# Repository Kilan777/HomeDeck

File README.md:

# Jarvis HomeDeck

> **Public mirror.** This is a snapshot of the private working repo (commit `f1d429f`). Some private parts of the software are not included.

A self-built voice assistant with a screen: a Raspberry Pi Compute Module 4 carrier PCB that bolts to the 7-inch
Raspberry Pi Touch Display 2, plus the software that turns it into "Jarvis". Personal project by Kilan.

The board carries the CM4, USB-C PD power, three 5 V bucks, a stereo class-D amplifier, two MEMS microphones,
a Camera Module 3 connector, CO2 / temperature / humidity / pressure / VOC sensors, an RGB LED bar and an external
WS2812B strip header, a fan header, buttons, a Qwiic-style I2C header, microSD, USB-A and a second USB-C.

The software is a single Python service with a module per feature and a touch UI in Chromium, plus a phone app
served on a personal domain behind Google sign-in. Voice runs on a local wake word and hosted speech models;
everything that is a command (timers, lights, music, volume, math) is handled on the device without a model.

| Folder | Contents |
|---|---|
| `kicad/` | KiCad project: hierarchical schematic (9 sheets), 4-layer routed PCB, project symbols and footprints, DRC rules |
| `tools/circuit.py` | The single source the schematic, netlist and BOM are generated from. Edit this, not the KiCad files |
| `out/` | Gerbers, JLCPCB BOM and pick-and-place, schematic PDF, board renders, DRC report (rev A as ordered) |
| `docs/` | Hardware docs: `README.md` (board overview), `ARCHITECTURE.md`, `BRINGUP.md`, `ORIENTATION.md`, and `PCB_ISSUES.md` (what went wrong on rev A and what rev B should change) |
| `software/homedeck/` | The assistant: `server.py`, `modules/`, `web/`, `install/`. See `docs/SOFTWARE.md` |
| `software/homedeck_ui.py` | The original bench dashboard used for bring-up (retired) |

## Status

- Rev A board #1 is fully working and in daily use, running at 9 V PD after two solder-jumper changes.
  Rev A board #2 is assembled and untested. Findings and the rev B list are in `docs/PCB_ISSUES.md`.
- Software is feature complete for daily use: home screen, Jarvis voice, Spotify (full client), YouTube (ad-free
  native player), air quality with history, timers, alarms, reminders, lists, calendar, countdowns, bikes, transit,
  flights radar, lights, fan, sleep sounds, guest card with Wi-Fi QR,
  presence, Wi-Fi setup, on-screen keyboard. See `docs/SOFTWARE.md`.

## Quick start

Hardware: order from `out/` (JLCPCB 4-layer, two-sided assembly), read `docs/BRINGUP.md`, then apply the rev A
fixes in `docs/PCB_ISSUES.md` before first power-on (the 9 V jumper setting matters).

Software, on the Pi:

```
rsync -a software/homedeck/ kilan@homedeck.local:~/hd/
ssh kilan@homedeck.local 'cd ~/hd && bash install.sh'
```

Then open Settings on the device for location, Wi-Fi, Spotify, calendar feeds and the API keys the optional
features need (Groq for voice, 511.org for Muni). Secrets live only on the device in `/var/lib/homedeck/config.json`
and are never in this repository.

## Privacy

This repository is private. It contains no credentials, tokens or Wi-Fi passwords. The device redacts secrets
from every API response, the phone app requires Google sign-in, and there is no VPN or third-party relay involved.

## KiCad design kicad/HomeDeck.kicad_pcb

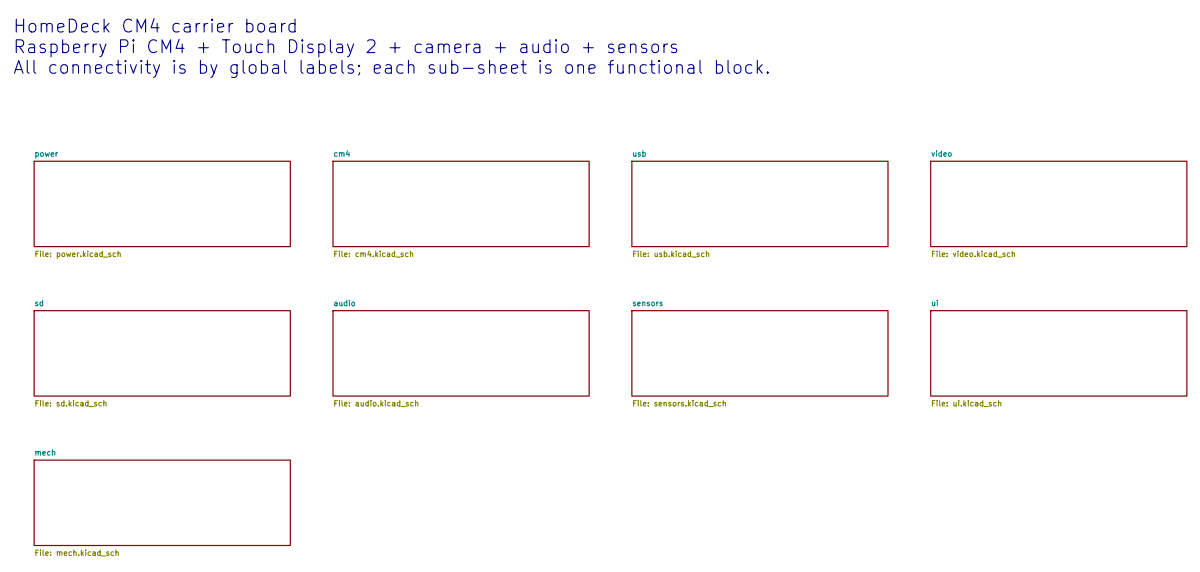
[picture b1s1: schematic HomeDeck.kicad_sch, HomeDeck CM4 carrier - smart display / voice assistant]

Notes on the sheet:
HomeDeck CM4 carrier board Raspberry Pi CM4 + Touch Display 2 + camera + audio + sensors All connectivity is by global labels; each sub-sheet is one functional block.

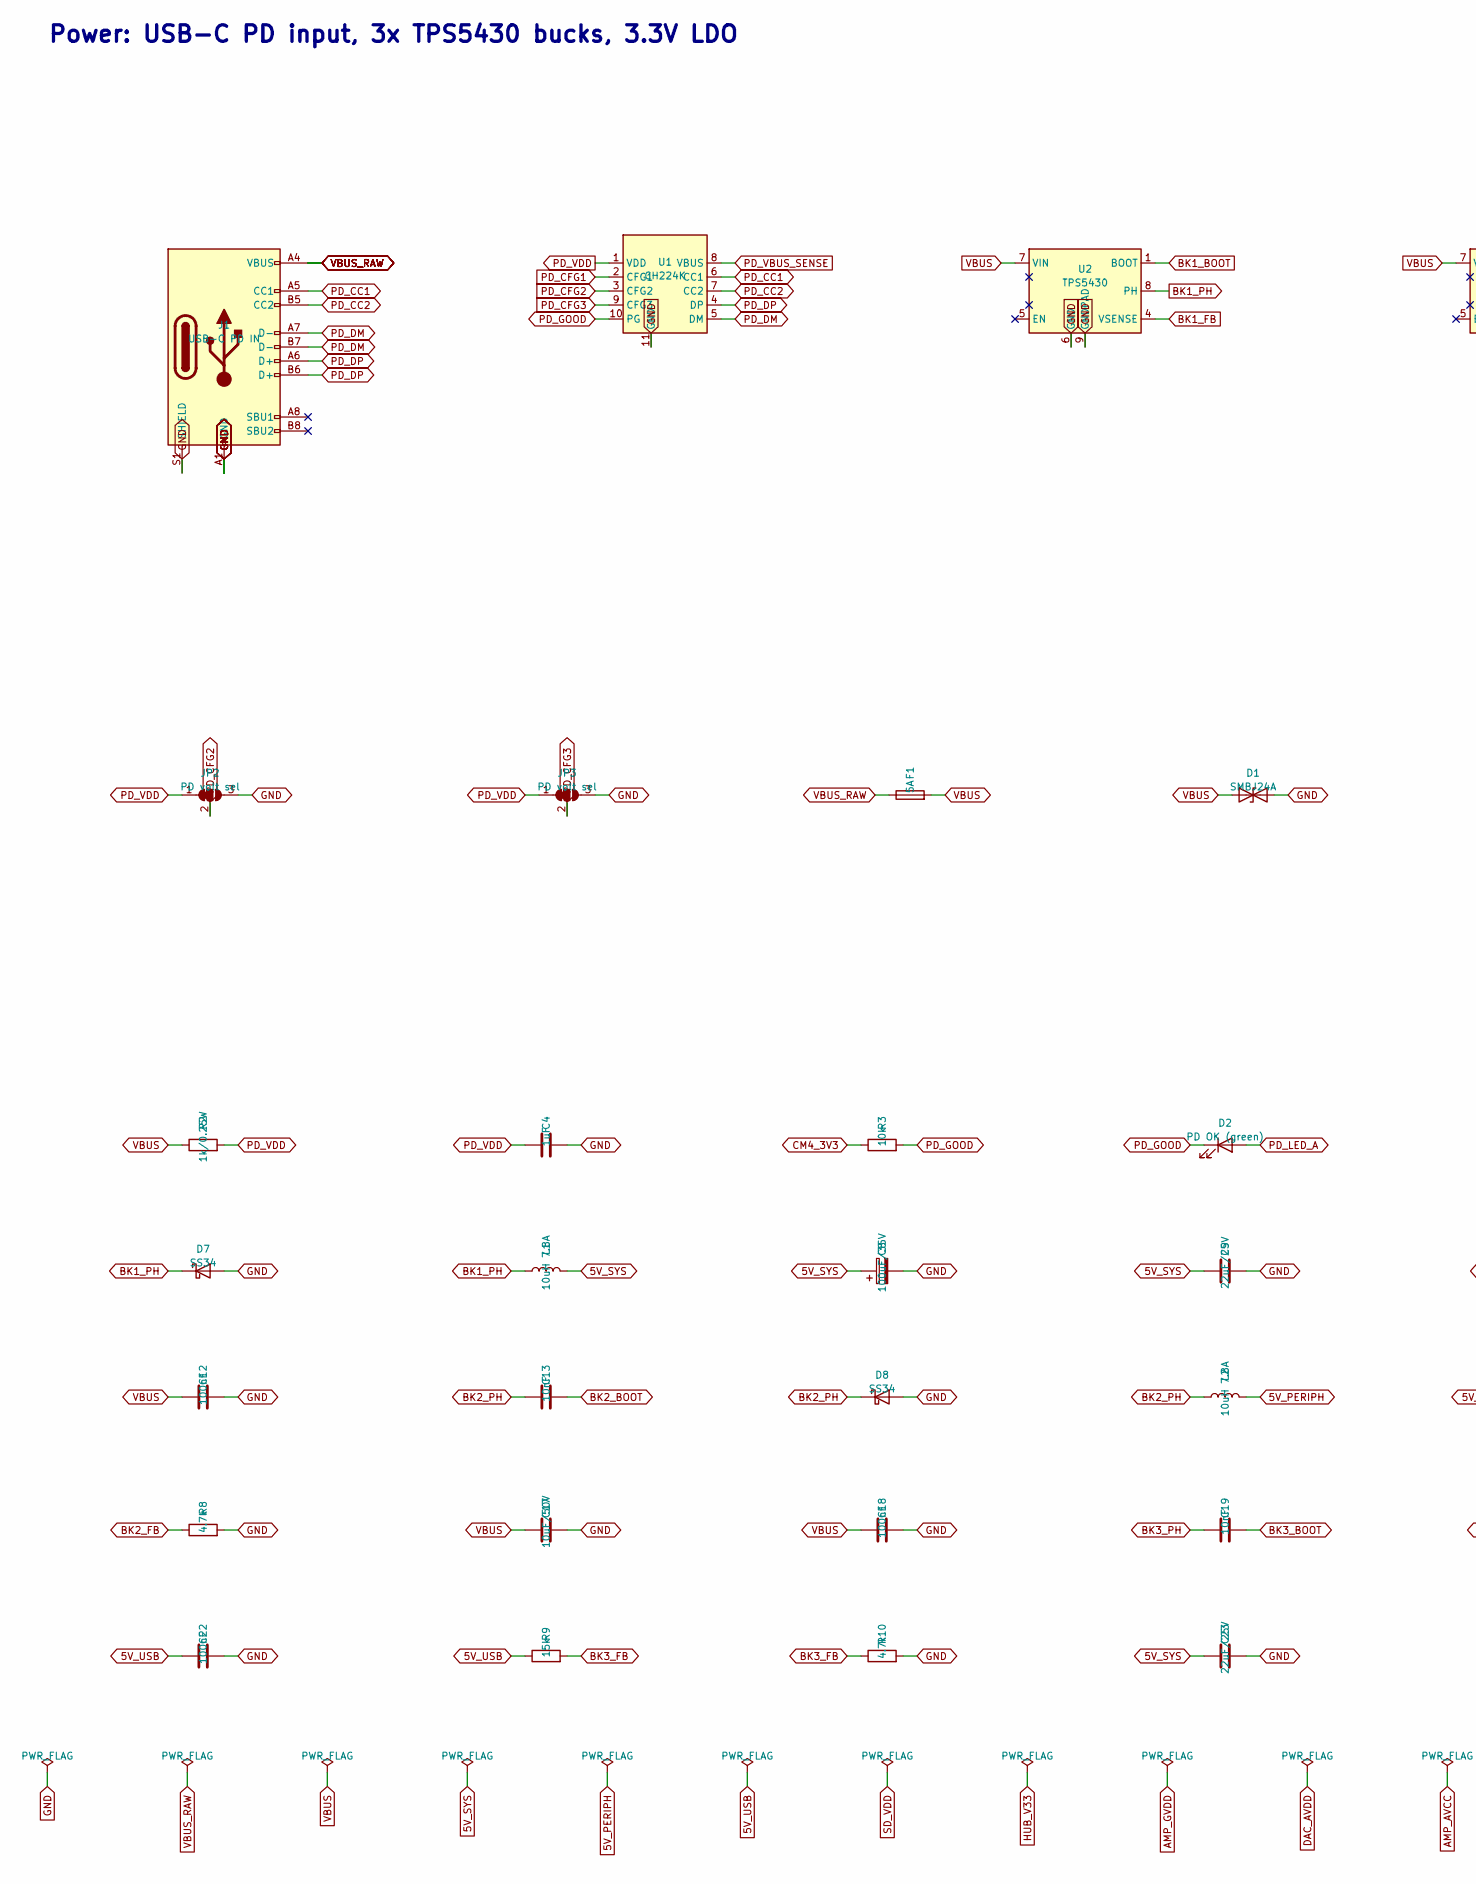
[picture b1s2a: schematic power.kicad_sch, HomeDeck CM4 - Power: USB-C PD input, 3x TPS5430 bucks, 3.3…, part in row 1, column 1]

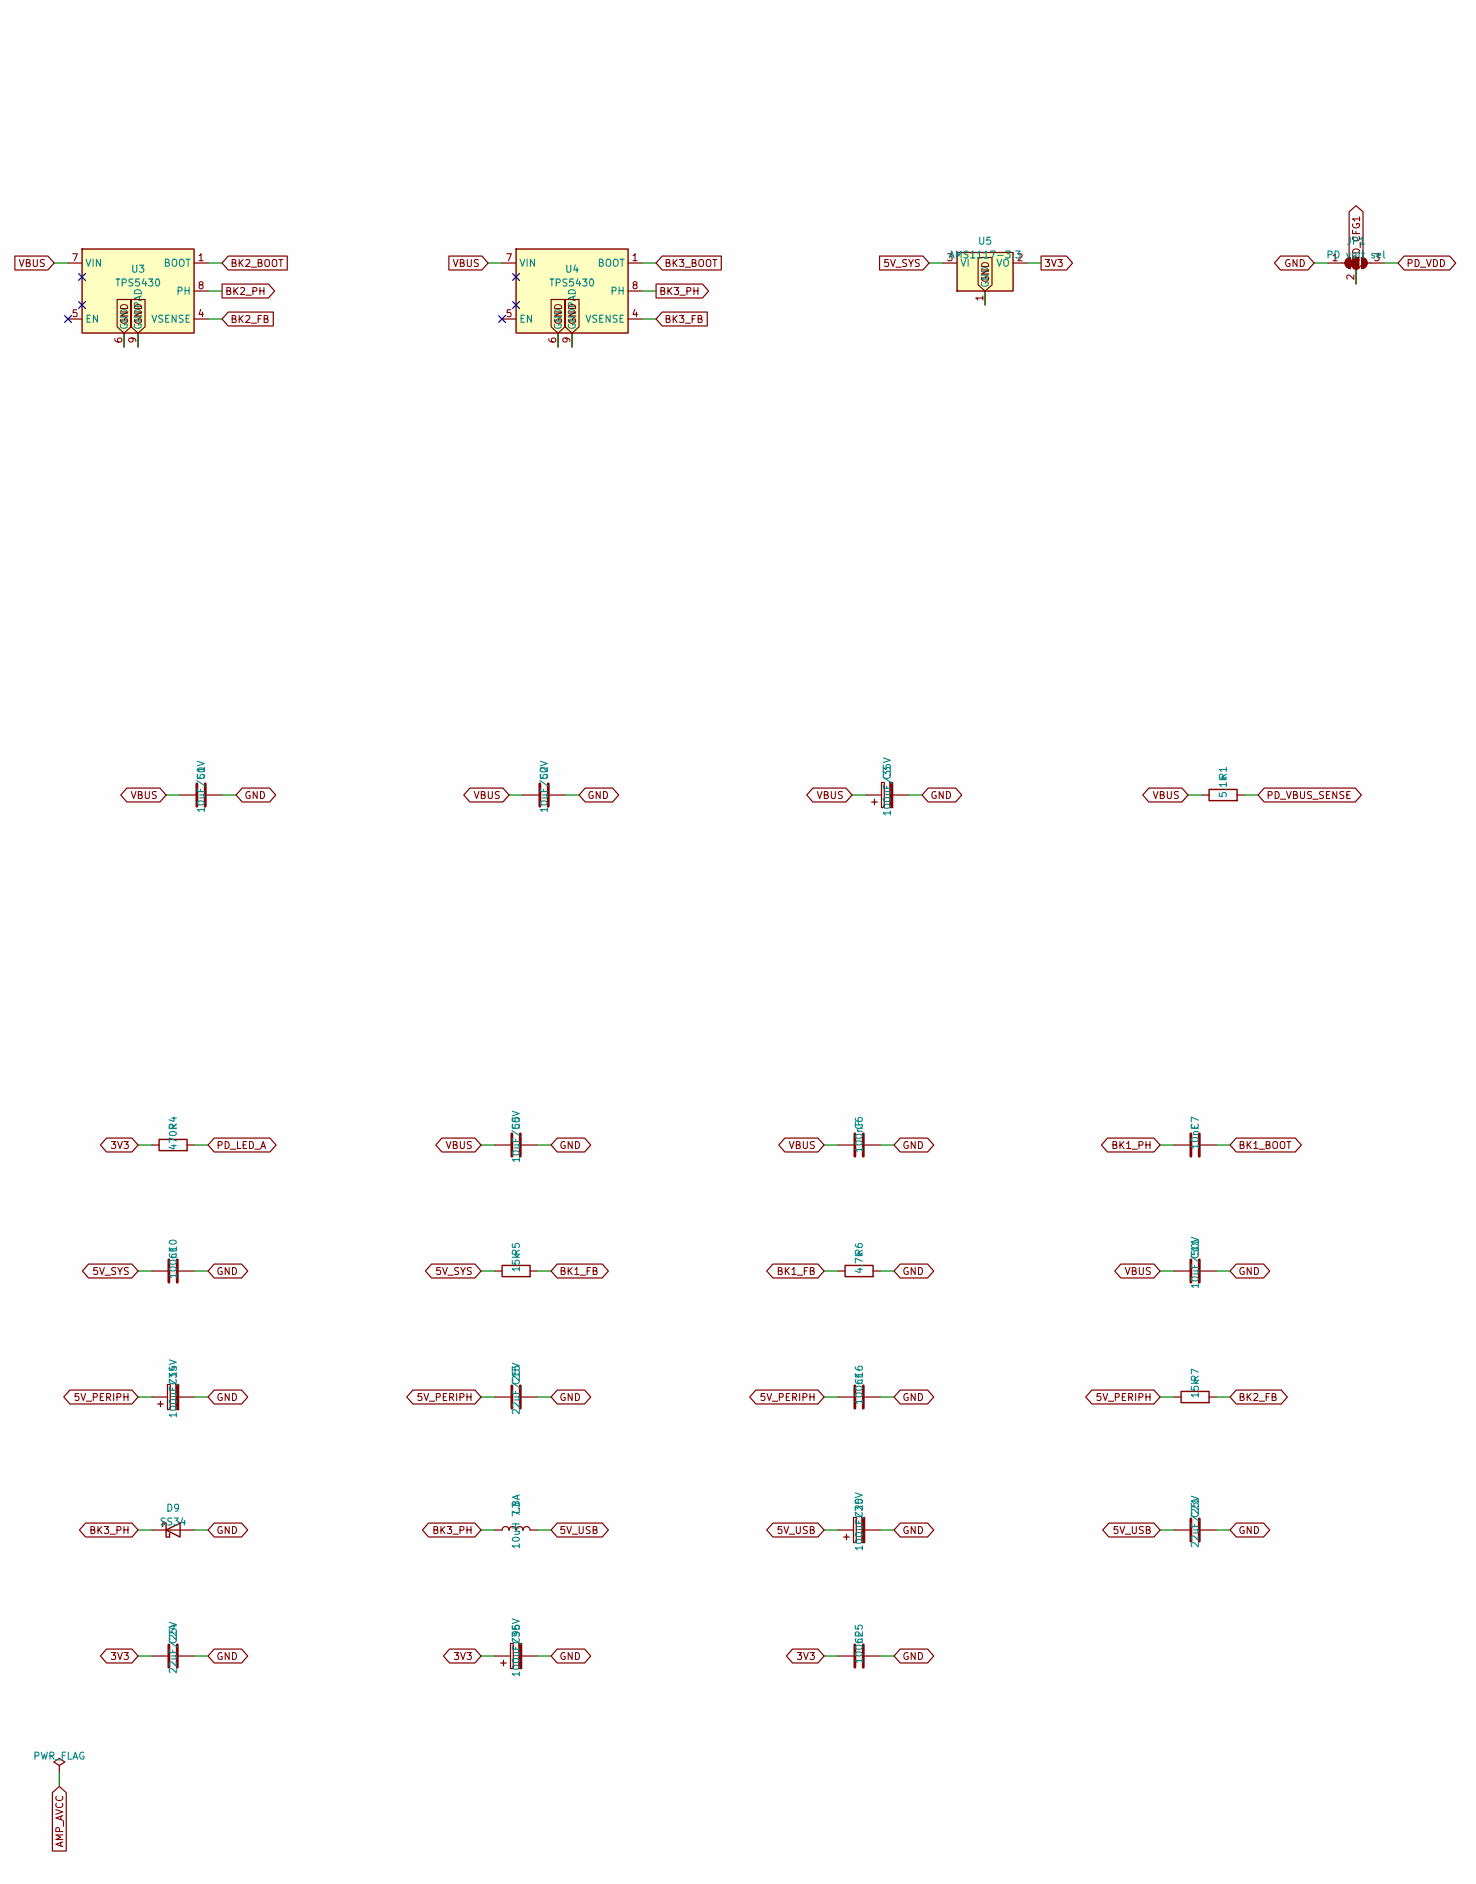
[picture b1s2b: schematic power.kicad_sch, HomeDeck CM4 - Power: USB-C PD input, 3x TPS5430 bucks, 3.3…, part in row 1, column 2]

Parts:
C1, C2, C5, C11, C17: 10uF/50V; C_1206_3216Metric; LCSC C13585
C3, C8, C14, C20, C96: 100uF/35V; CP_Elec_6.3x7.7; LCSC C3339
C4: 1uF; C_0603_1608Metric; LCSC C15849
C6, C10, C12, C16, C18, C22, C25: 100nF; C_0603_1608Metric; LCSC C14663
C7, C13, C19: 10nF; C_0603_1608Metric; LCSC C57112
C9, C15, C21, C23, C24: 22uF/25V; C_1206_3216Metric; LCSC C12891
D1: SMBJ24A; D_SMB; MPN SMBJ24A; LCSC C87268
D2: PD OK (green); LED_0805_2012Metric; MPN KT-0805G; LCSC C2297
D7, D8, D9: SS34; D_SMA; MPN SS34; LCSC C8678
F1: 5A; Fuse_1206_3216Metric; MPN SF-1206F500-2; LCSC C48332
J1: USB-C PD IN; USB_C_Receptacle_HRO_TYPE-C-31-M-12; MPN TYPE-C-31-M-12; LCSC C165948
JP1, JP2, JP3: PD volt sel; SolderJumper-3_P1.3mm_Bridged12_RoundedPad1.0x1.5mm
L1, L2, L3: 10uH 7.8A; L_Sunlord_MWSA1004S; MPN MWSA1004S-100MT; LCSC C408487
R1: 5.1k; R_0603_1608Metric; LCSC C23186
R2: 1k/0.25W; R_1206_3216Metric; LCSC C4410
R3: 10k; R_0603_1608Metric; LCSC C25804
R4: 470R; R_0603_1608Metric; LCSC C23179
R5, R7, R9: 15k; R_0603_1608Metric; LCSC C22809
R6, R8, R10: 4.7k; R_0603_1608Metric; LCSC C23162
U1: CH224K; ESSOP-10-1EP_3.9x4.9mm_P1.0mm; MPN CH224K; LCSC C970725
U2, U3, U4: TPS5430; TI_SO-PowerPAD-8_ThermalVias; MPN TPS5430DDAR; LCSC C9864
U5: AMS1117-3.3; SOT-223-3_TabPin2; MPN AMS1117-3.3; LCSC C6186

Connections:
3V3: C24.1, C25.1, C96.1, R4.1, U5.2 (VO); also elsewhere on the board
5V_PERIPH: C14.1, C15.1, C16.1, L2.2, R7.1; also elsewhere on the board
5V_SYS: C8.1, C9.1, C10.1, C23.1, L1.2, R5.1, U5.3 (VI); also elsewhere on the board
5V_USB: C20.1, C21.1, C22.1, L3.2, R9.1; also elsewhere on the board
BK1_BOOT: C7.2, U2.1 (BOOT)
BK1_FB: R5.2, R6.1, U2.4 (VSENSE)
BK1_PH: C7.1, D7.1 (K), L1.1, U2.8 (PH)
BK2_BOOT: C13.2, U3.1 (BOOT)
BK2_FB: R7.2, R8.1, U3.4 (VSENSE)
BK2_PH: C13.1, D8.1 (K), L2.1, U3.8 (PH)
BK3_BOOT: C19.2, U4.1 (BOOT)
BK3_FB: R9.2, R10.1, U4.4 (VSENSE)
BK3_PH: C19.1, D9.1 (K), L3.1, U4.8 (PH)
CM4_3V3: R3.1; also elsewhere on the board
GND: C1.2, C2.2, C3.2, C4.2, C5.2, C6.2, C8.2, C9.2, C10.2, C11.2, C12.2, C14.2, C15.2, C16.2, C17.2, C18.2, C20.2, C21.2, C22.2, C23.2, C24.2, C25.2, C96.2, D1.2 (A2), D7.2 (A), D8.2 (A), D9.2 (A), J1.A1 (GND), J1.A12 (GND), J1.B1 (GND), J1.B12 (GND), J1.S1 (SHIELD), JP1.1 (A), JP2.3 (B), JP3.3 (B), R6.2, R8.2, R10.2, U1.11 (GND), U2.6 (GND), U2.9 (GNDPAD), U3.6 (GND), U3.9 (GNDPAD), U4.6 (GND), U4.9 (GNDPAD), U5.1 (GND); also elsewhere on the board
PD_CC1: J1.A5 (CC1), U1.6 (CC1)
PD_CC2: J1.B5 (CC2), U1.7 (CC2)
PD_CFG1: JP1.2 (C), U1.2 (CFG1)
PD_CFG2: JP2.2 (C), U1.3 (CFG2)
PD_CFG3: JP3.2 (C), U1.9 (CFG3)
PD_DM: J1.A7 (D-), J1.B7 (D-), U1.5 (DM)
PD_DP: J1.A6 (D+), J1.B6 (D+), U1.4 (DP)
PD_GOOD: D2.1 (K), R3.2, U1.10 (PG); also elsewhere on the board
PD_LED_A: D2.2 (A), R4.2
PD_VBUS_SENSE: R1.2, U1.8 (VBUS)
PD_VDD: C4.1, JP1.3 (B), JP2.1 (A), JP3.1 (A), R2.2, U1.1 (VDD)
VBUS: C1.1, C2.1, C3.1, C5.1, C6.1, C11.1, C12.1, C17.1, C18.1, D1.1 (A1), F1.2, R1.1, R2.1, U2.7 (VIN), U3.7 (VIN), U4.7 (VIN); also elsewhere on the board
VBUS_RAW: F1.1, J1.A4 (VBUS), J1.A9 (VBUS), J1.B4 (VBUS), J1.B9 (VBUS)

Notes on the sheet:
Power: USB-C PD input, 3x TPS5430 bucks, 3.3V LDO

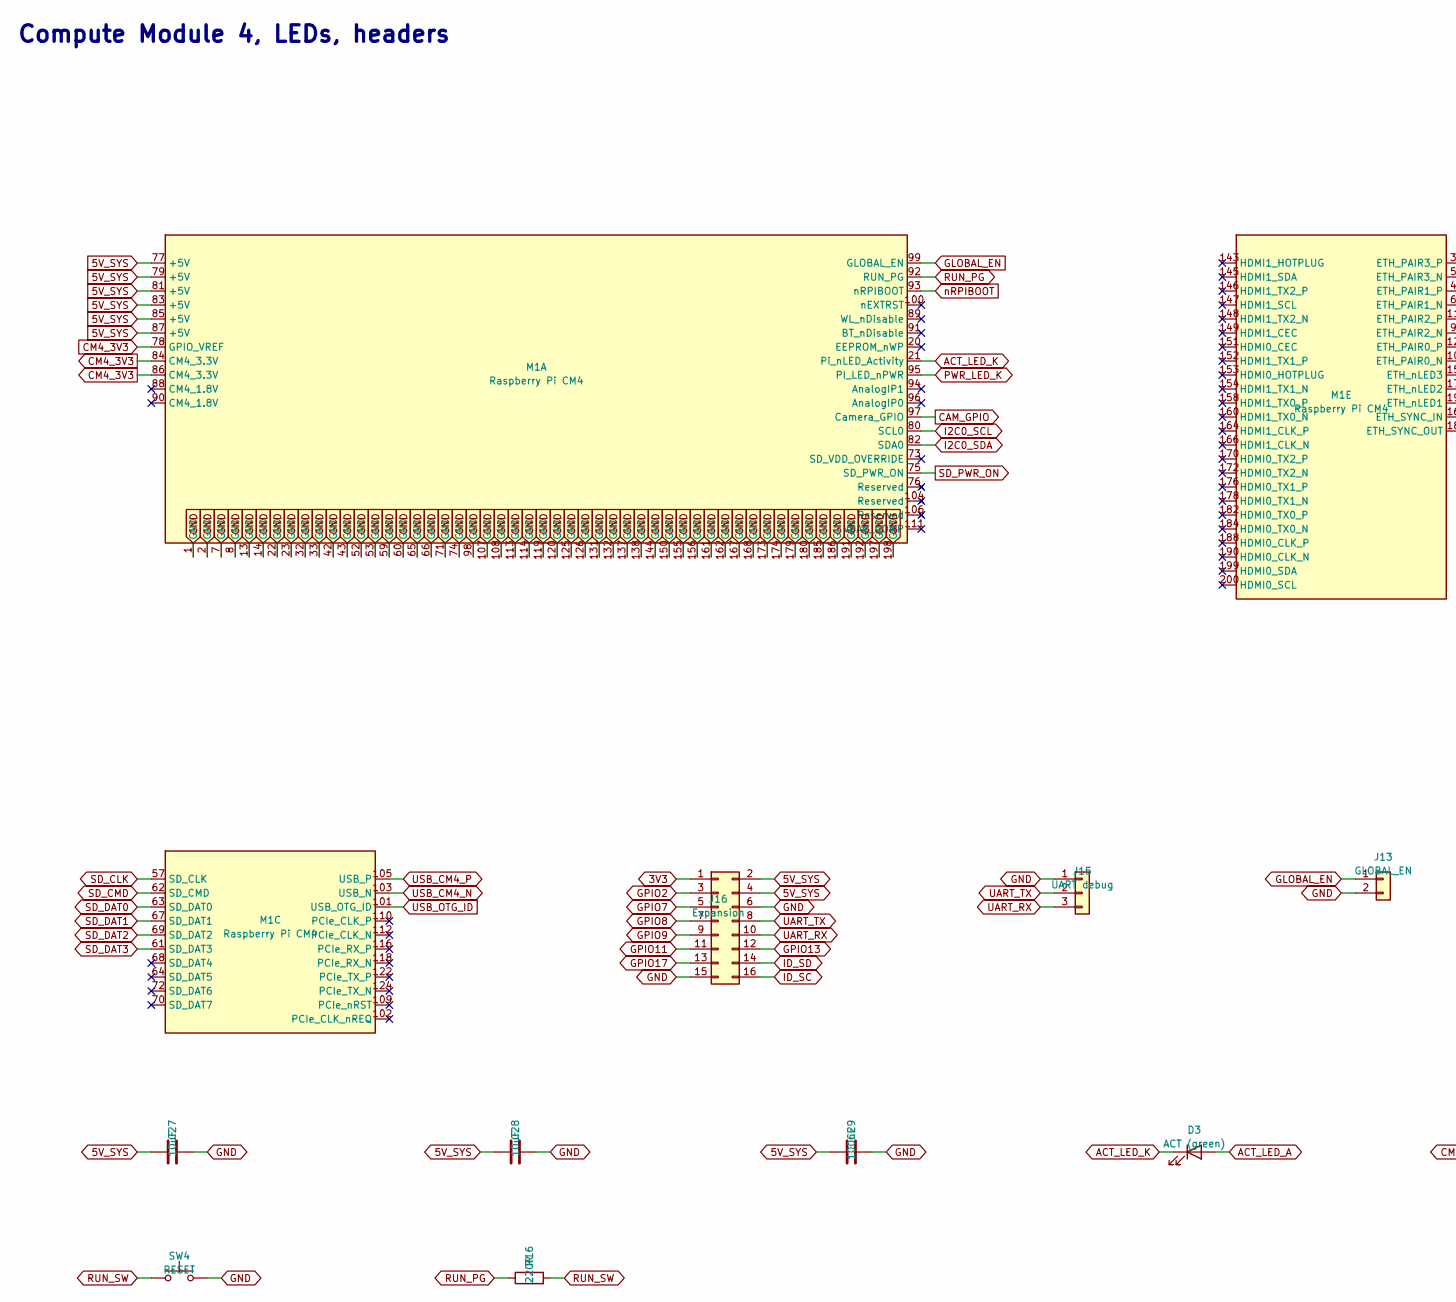
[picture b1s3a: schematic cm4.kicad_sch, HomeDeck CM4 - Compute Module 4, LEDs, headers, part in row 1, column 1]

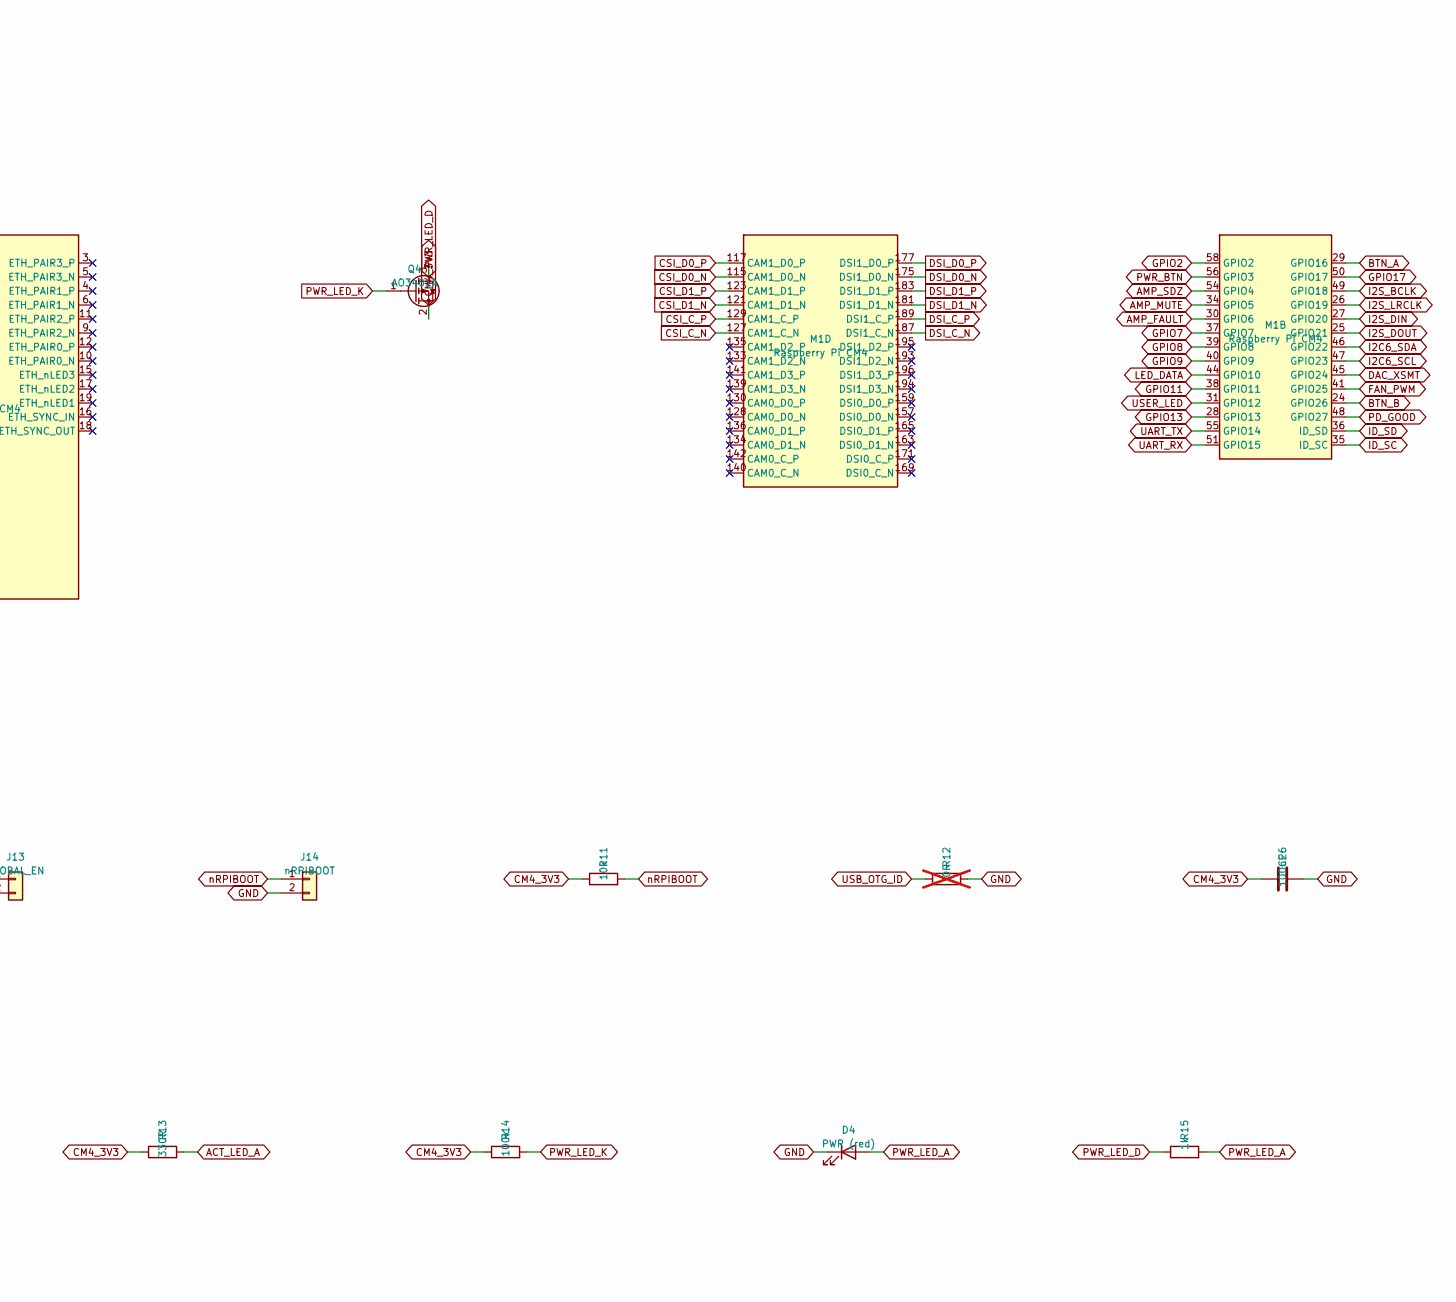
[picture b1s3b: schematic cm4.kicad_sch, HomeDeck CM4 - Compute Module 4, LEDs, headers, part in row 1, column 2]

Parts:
C26, C29: 100nF; C_0603_1608Metric; LCSC C14663
C27, C28: 10uF; C_0603_1608Metric; LCSC C96446
D3: ACT (green); LED_0805_2012Metric; MPN KT-0805G; LCSC C2297
D4: PWR (red); LED_0603_1608Metric; MPN KT-0603R; LCSC C2286
J13: GLOBAL_EN; PinHeader_1x02_P2.54mm_Vertical; MPN B-2100S02P-A110; LCSC C124375
J14: nRPIBOOT; PinHeader_1x02_P2.54mm_Vertical; MPN B-2100S02P-A110; LCSC C124375
J15: UART debug; PinHeader_1x03_P2.54mm_Vertical; MPN B-2100S03P-A110; LCSC C124376
J16: Expansion; PinHeader_2x08_P2.54mm_Vertical; MPN PZ254V-12-16P; LCSC C492425
M1: Raspberry Pi CM4; RPi_CM4; MPN CM4
Q4: AO3401A; SOT-23; MPN AO3401A; LCSC C15127
R11: 10k; R_0603_1608Metric; LCSC C25804
R12: 0R; R_0603_1608Metric; LCSC C21189; not fitted
R13: 330R; R_0603_1608Metric; LCSC C23138
R14: 100k; R_0603_1608Metric; LCSC C25803
R15: 1k; R_0603_1608Metric; LCSC C21190
R16: 220R; R_0603_1608Metric; LCSC C22962
SW4: RESET; SW_Push_1P1T_XKB_TS-1187A; MPN TS-1187A-B-A-B; LCSC C318884

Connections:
3V3: J16.1; also elsewhere on the board
5V_SYS: C27.1, C28.1, C29.1, J16.2, J16.4, M1.77 (+5V), M1.79 (+5V), M1.81 (+5V), M1.83 (+5V), M1.85 (+5V), M1.87 (+5V); also elsewhere on the board
ACT_LED_A: D3.2 (A), R13.2
ACT_LED_K: D3.1 (K), M1.21 (Pi_nLED_Activity)
AMP_FAULT: M1.30 (GPIO6); also elsewhere on the board
AMP_MUTE: M1.34 (GPIO5); also elsewhere on the board
AMP_SDZ: M1.54 (GPIO4); also elsewhere on the board
BTN_A: M1.29 (GPIO16); also elsewhere on the board
BTN_B: M1.24 (GPIO26); also elsewhere on the board
CAM_GPIO: M1.97 (Camera_GPIO); also elsewhere on the board
CM4_3V3: C26.1, M1.78 (GPIO_VREF), M1.84 (CM4_3.3V), M1.86 (CM4_3.3V), Q4.2 (S), R11.1, R13.1, R14.1; also elsewhere on the board
CSI_C_N: M1.127 (CAM1_C_N); also elsewhere on the board
CSI_C_P: M1.129 (CAM1_C_P); also elsewhere on the board
CSI_D0_N: M1.115 (CAM1_D0_N); also elsewhere on the board
CSI_D0_P: M1.117 (CAM1_D0_P); also elsewhere on the board
CSI_D1_N: M1.121 (CAM1_D1_N); also elsewhere on the board
CSI_D1_P: M1.123 (CAM1_D1_P); also elsewhere on the board
DAC_XSMT: M1.45 (GPIO24); also elsewhere on the board
DSI_C_N: M1.187 (DSI1_C_N); also elsewhere on the board
DSI_C_P: M1.189 (DSI1_C_P); also elsewhere on the board
DSI_D0_N: M1.175 (DSI1_D0_N); also elsewhere on the board
DSI_D0_P: M1.177 (DSI1_D0_P); also elsewhere on the board
DSI_D1_N: M1.181 (DSI1_D1_N); also elsewhere on the board
DSI_D1_P: M1.183 (DSI1_D1_P); also elsewhere on the board
FAN_PWM: M1.41 (GPIO25); also elsewhere on the board
GLOBAL_EN: J13.1, M1.99 (GLOBAL_EN)
GND: C26.2, C27.2, C28.2, C29.2, D4.1 (K), J13.2, J14.2, J15.1, J16.6, J16.15, M1.1 (GND), M1.2 (GND), M1.7 (GND), M1.8 (GND), M1.13 (GND), M1.14 (GND), M1.22 (GND), M1.23 (GND), M1.32 (GND), M1.33 (GND), M1.42 (GND), M1.43 (GND), M1.52 (GND), M1.53 (GND), M1.59 (GND), M1.60 (GND), M1.65 (GND), M1.66 (GND), M1.71 (GND), M1.74 (GND), M1.98 (GND), M1.107 (GND), M1.108 (GND), M1.113 (GND), M1.114 (GND), M1.119 (GND), M1.120 (GND), M1.125 (GND), M1.126 (GND), M1.131 (GND), M1.132 (GND), M1.137 (GND), M1.138 (GND), M1.144 (GND), M1.150 (GND), M1.155 (GND), M1.156 (GND), M1.161 (GND), M1.162 (GND), M1.167 (GND), M1.168 (GND), M1.173 (GND), M1.174 (GND), M1.179 (GND), M1.180 (GND), M1.185 (GND), M1.186 (GND), M1.191 (GND), M1.192 (GND), M1.197 (GND), M1.198 (GND), R12.2, SW4.2; also elsewhere on the board
GPIO2: J16.3, M1.58 (GPIO2)
GPIO7: J16.5, M1.37 (GPIO7)
GPIO8: J16.7, M1.39 (GPIO8)
GPIO9: J16.9, M1.40 (GPIO9)
GPIO11: J16.11, M1.38 (GPIO11)
GPIO13: J16.12, M1.28 (GPIO13)
GPIO17: J16.13, M1.50 (GPIO17)
I2C0_SCL: M1.80 (SCL0); also elsewhere on the board
I2C0_SDA: M1.82 (SDA0); also elsewhere on the board
I2C6_SCL: M1.47 (GPIO23); also elsewhere on the board
I2C6_SDA: M1.46 (GPIO22); also elsewhere on the board
I2S_BCLK: M1.49 (GPIO18); also elsewhere on the board
I2S_DIN: M1.27 (GPIO20); also elsewhere on the board
I2S_DOUT: M1.25 (GPIO21); also elsewhere on the board
I2S_LRCLK: M1.26 (GPIO19); also elsewhere on the board
ID_SC: J16.16, M1.35 (ID_SC)
ID_SD: J16.14, M1.36 (ID_SD)
LED_DATA: M1.44 (GPIO10); also elsewhere on the board
PD_GOOD: M1.48 (GPIO27); also elsewhere on the board
PWR_BTN: M1.56 (GPIO3); also elsewhere on the board
PWR_LED_A: D4.2 (A), R15.2
PWR_LED_D: Q4.3 (D), R15.1
PWR_LED_K: M1.95 (PI_LED_nPWR), Q4.1 (G), R14.2
RUN_PG: M1.92 (RUN_PG), R16.1
RUN_SW: R16.2, SW4.1
SD_CLK: M1.57 (SD_CLK); also elsewhere on the board
SD_CMD: M1.62 (SD_CMD); also elsewhere on the board
SD_DAT0: M1.63 (SD_DAT0); also elsewhere on the board
SD_DAT1: M1.67 (SD_DAT1); also elsewhere on the board
SD_DAT2: M1.69 (SD_DAT2); also elsewhere on the board
SD_DAT3: M1.61 (SD_DAT3); also elsewhere on the board
SD_PWR_ON: M1.75 (SD_PWR_ON); also elsewhere on the board
UART_RX: J15.3, J16.10, M1.51 (GPIO15)
UART_TX: J15.2, J16.8, M1.55 (GPIO14)
USB_CM4_N: M1.103 (USB_N); also elsewhere on the board
USB_CM4_P: M1.105 (USB_P); also elsewhere on the board
USB_OTG_ID: M1.101 (USB_OTG_ID), R12.1
USER_LED: M1.31 (GPIO12); also elsewhere on the board
nRPIBOOT: J14.1, M1.93 (nRPIBOOT), R11.2; also elsewhere on the board

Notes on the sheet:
Compute Module 4, LEDs, headers

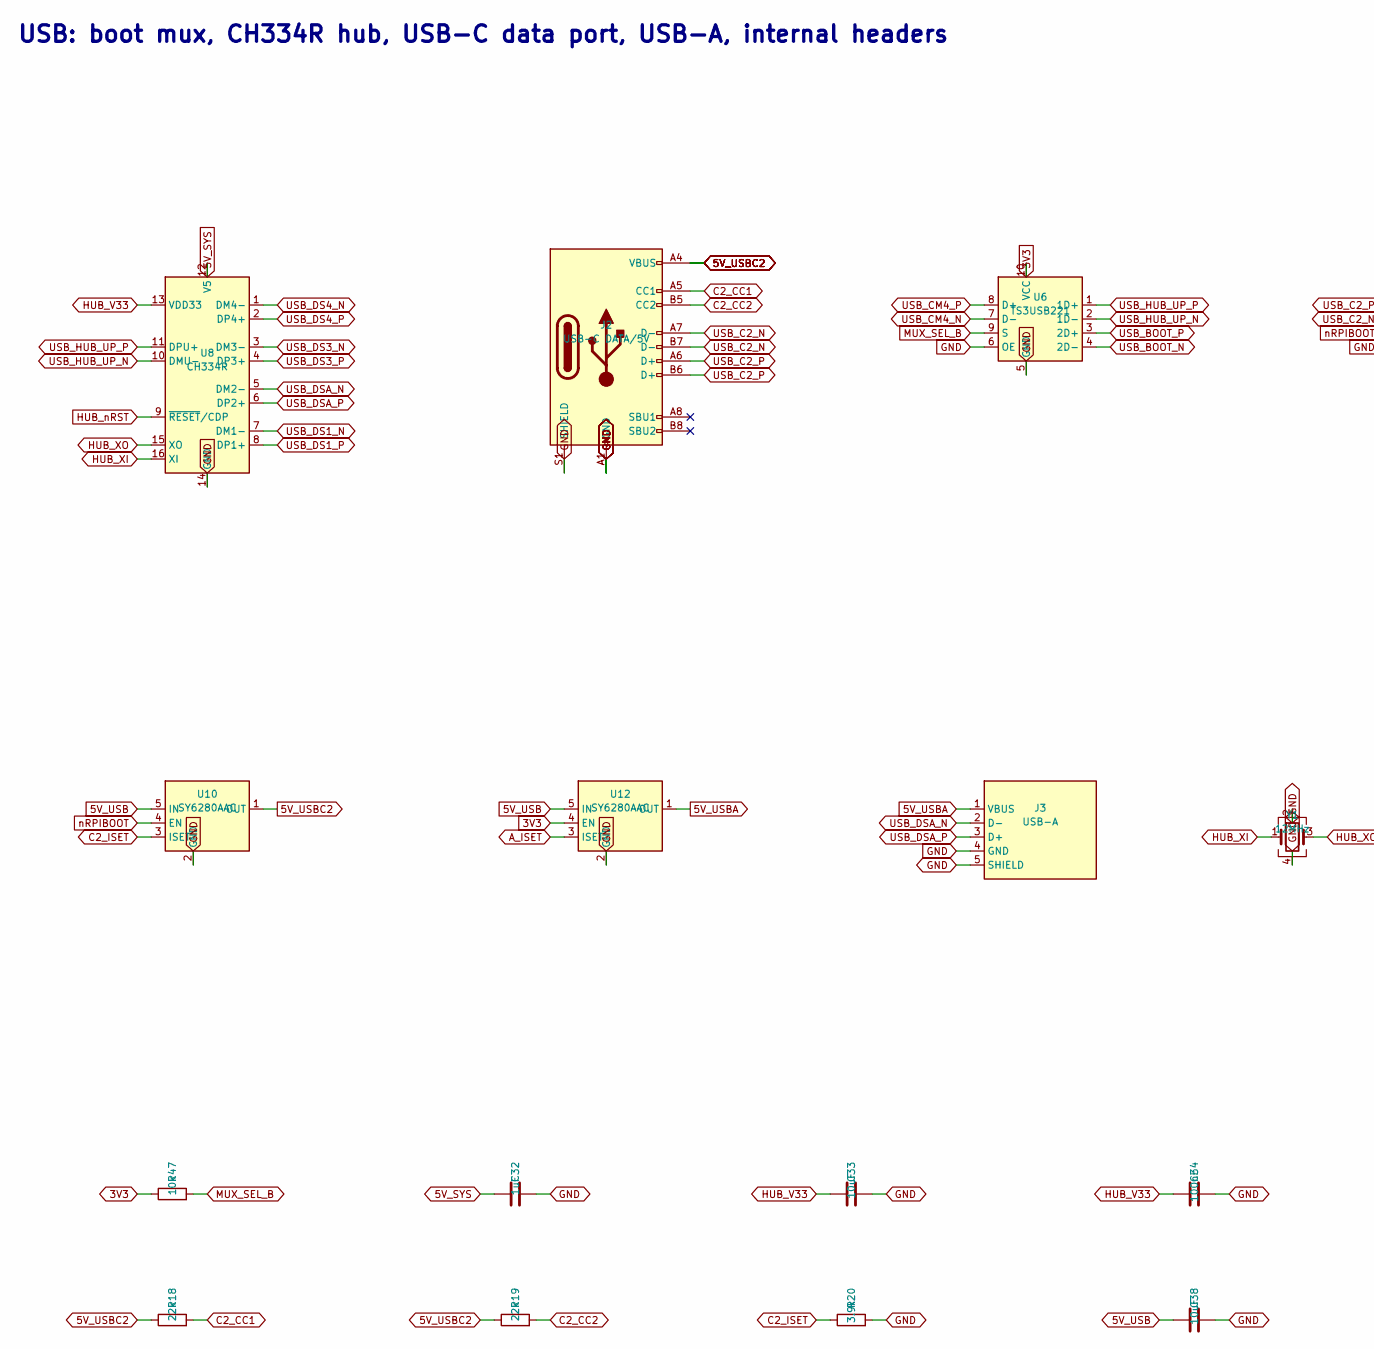
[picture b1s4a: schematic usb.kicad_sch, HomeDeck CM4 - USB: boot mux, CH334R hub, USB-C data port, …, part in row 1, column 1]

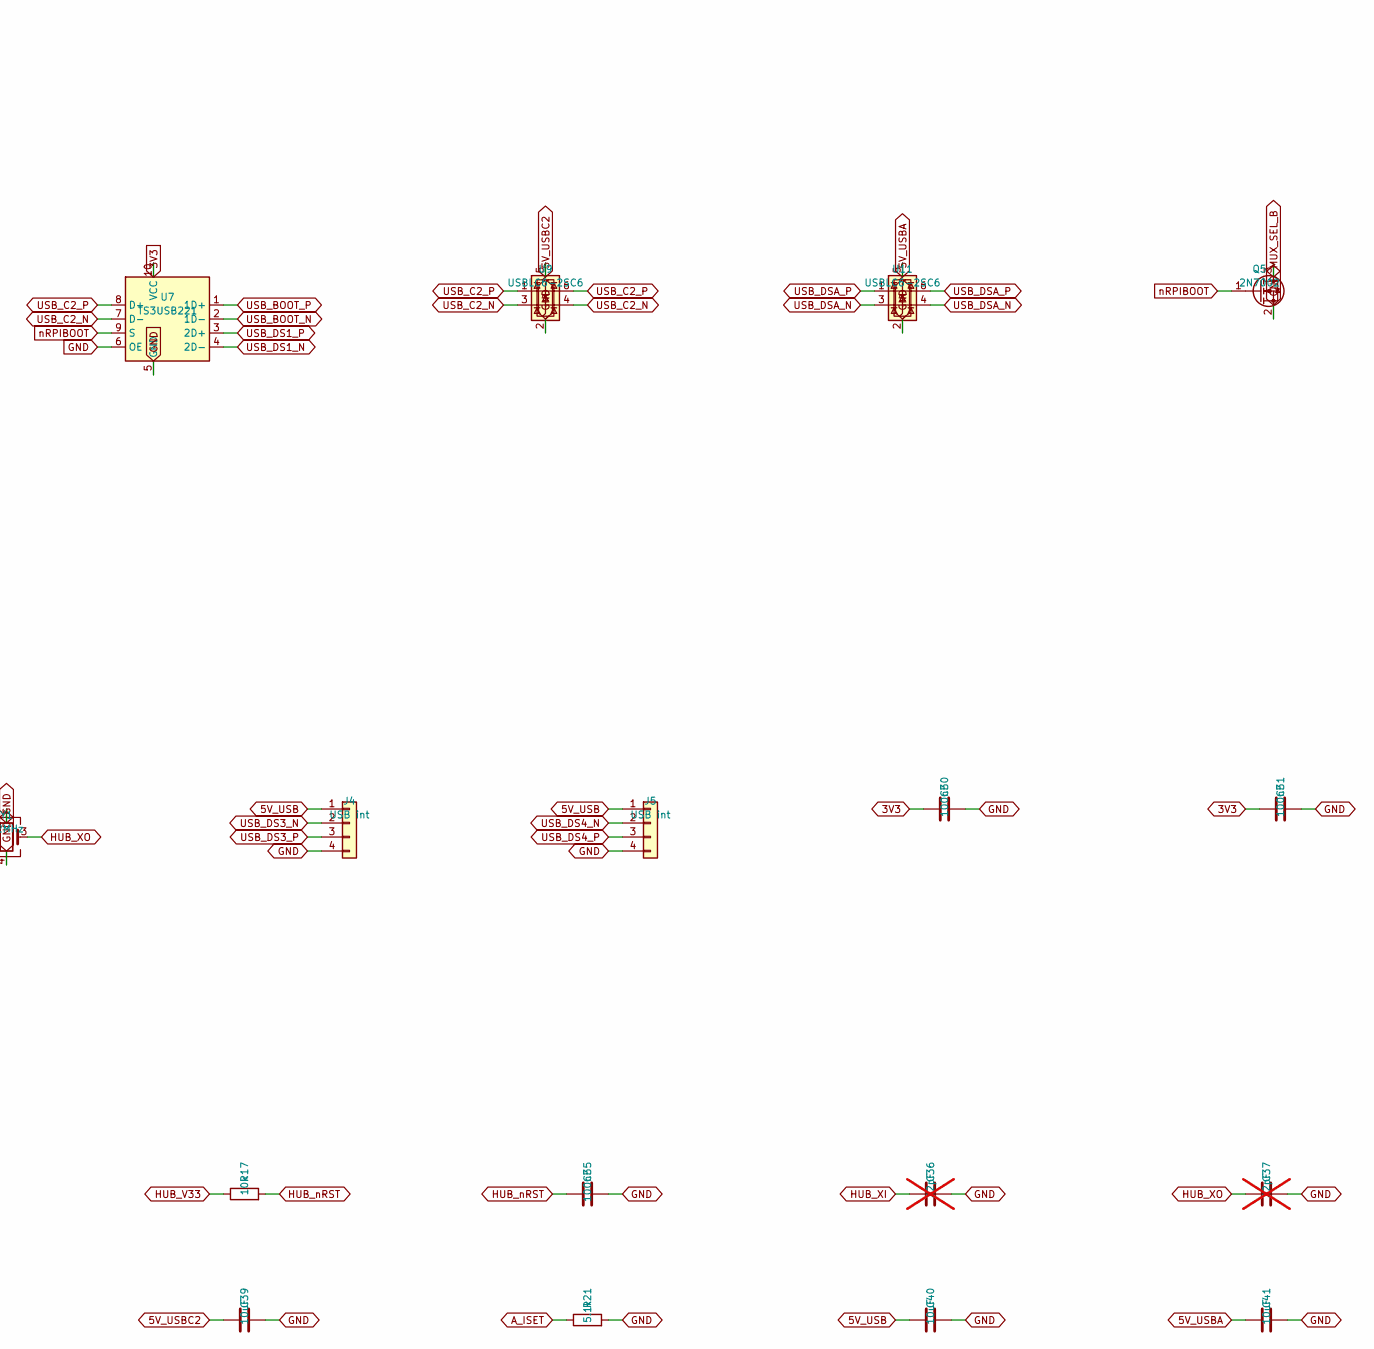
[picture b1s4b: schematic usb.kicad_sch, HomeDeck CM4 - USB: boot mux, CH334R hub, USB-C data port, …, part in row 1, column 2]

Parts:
C30, C31, C34, C35: 100nF; C_0603_1608Metric; LCSC C14663
C32: 1uF; C_0603_1608Metric; LCSC C15849
C33, C38, C39, C40, C41: 10uF; C_0603_1608Metric; LCSC C96446
C36, C37: 22pF; C_0603_1608Metric; LCSC C1653; not fitted
J2: USB-C DATA/5V; USB_C_Receptacle_HRO_TYPE-C-31-M-12; MPN TYPE-C-31-M-12; LCSC C165948
J3: USB-A; USB_A_Molex_67643_Horizontal; MPN 901-211A1021D10100; LCSC C2346
J4, J5: USB int; PinHeader_1x04_P2.54mm_Vertical; MPN B-2100S04P-A110; LCSC C124378
Q5: 2N7002; SOT-23; MPN 2N7002; LCSC C8545
R17, R47: 10k; R_0603_1608Metric; LCSC C25804
R18, R19: 22k; R_0603_1608Metric; LCSC C31850
R20: 3.9k; R_0603_1608Metric; LCSC C23018
R21: 5.1k; R_0603_1608Metric; LCSC C23186
U6, U7: TS3USB221; Texas_UQFN-10_1.5x2mm_P0.5mm; MPN TS3USB221RSER; LCSC C130085
U8: CH334R; QSOP-16_3.9x4.9mm_P0.635mm; MPN CH334R; LCSC C4154405
U9, U11: USBLC6-2SC6; SOT-23-6; MPN USBLC6-2SC6; LCSC C7519
U10, U12: SY6280AAC; SOT-23-5; MPN SY6280AAC; LCSC C55136
Y1: 12MHz; Crystal_SMD_3225-4Pin_3.2x2.5mm; MPN X322512MSB4SI; LCSC C9002

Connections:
3V3: C30.1, C31.1, R47.1, U6.10 (VCC), U7.10 (VCC), U12.4 (EN); also elsewhere on the board
5V_SYS: C32.1, U8.12 (V5); also elsewhere on the board
5V_USB: C38.1, C40.1, J4.1, J5.1, U10.5 (IN), U12.5 (IN); also elsewhere on the board
5V_USBA: C41.1, J3.1 (VBUS), U11.5 (VBUS), U12.1 (OUT)
5V_USBC2: C39.1, J2.A4 (VBUS), J2.A9 (VBUS), J2.B4 (VBUS), J2.B9 (VBUS), R18.1, R19.1, U9.5 (VBUS), U10.1 (OUT)
A_ISET: R21.1, U12.3 (ISET)
C2_CC1: J2.A5 (CC1), R18.2
C2_CC2: J2.B5 (CC2), R19.2
C2_ISET: R20.1, U10.3 (ISET)
GND: C30.2, C31.2, C32.2, C33.2, C34.2, C35.2, C36.2, C37.2, C38.2, C39.2, C40.2, C41.2, J2.A1 (GND), J2.A12 (GND), J2.B1 (GND), J2.B12 (GND), J2.S1 (SHIELD), J3.4 (GND), J3.5 (SHIELD), J4.4, J5.4, Q5.2 (S), R20.2, R21.2, U6.5 (GND), U6.6 (OE), U7.5 (GND), U7.6 (OE), U8.14 (GND), U9.2 (GND), U10.2 (GND), U11.2 (GND), U12.2 (GND), Y1.2, Y1.4; also elsewhere on the board
HUB_V33: C33.1, C34.1, R17.1, U8.13 (VDD33)
HUB_XI: C36.1, U8.16 (XI), Y1.1
HUB_XO: C37.1, U8.15 (XO), Y1.3
HUB_nRST: C35.1, R17.2, U8.9 (~RESET/CDP)
MUX_SEL_B: Q5.3 (D), R47.2, U6.9 (S)
USB_BOOT_N: U6.4 (2D-), U7.2 (1D-)
USB_BOOT_P: U6.3 (2D+), U7.1 (1D+)
USB_C2_N: J2.A7 (D-), J2.B7 (D-), U7.7 (D-), U9.3 (I/O2), U9.4 (I/O2)
USB_C2_P: J2.A6 (D+), J2.B6 (D+), U7.8 (D+), U9.1 (I/O1), U9.6 (I/O1)
USB_CM4_N: U6.7 (D-); also elsewhere on the board
USB_CM4_P: U6.8 (D+); also elsewhere on the board
USB_DS1_N: U7.4 (2D-), U8.7 (DM1-)
USB_DS1_P: U7.3 (2D+), U8.8 (DP1+)
USB_DS3_N: J4.2, U8.3 (DM3-)
USB_DS3_P: J4.3, U8.4 (DP3+)
USB_DS4_N: J5.2, U8.1 (DM4-)
USB_DS4_P: J5.3, U8.2 (DP4+)
USB_DSA_N: J3.2 (D-), U8.5 (DM2-), U11.3 (I/O2), U11.4 (I/O2)
USB_DSA_P: J3.3 (D+), U8.6 (DP2+), U11.1 (I/O1), U11.6 (I/O1)
USB_HUB_UP_N: U6.2 (1D-), U8.10 (DMU-)
USB_HUB_UP_P: U6.1 (1D+), U8.11 (DPU+)
nRPIBOOT: Q5.1 (G), U7.9 (S), U10.4 (EN); also elsewhere on the board

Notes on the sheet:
USB: boot mux, CH334R hub, USB-C data port, USB-A, internal headers
